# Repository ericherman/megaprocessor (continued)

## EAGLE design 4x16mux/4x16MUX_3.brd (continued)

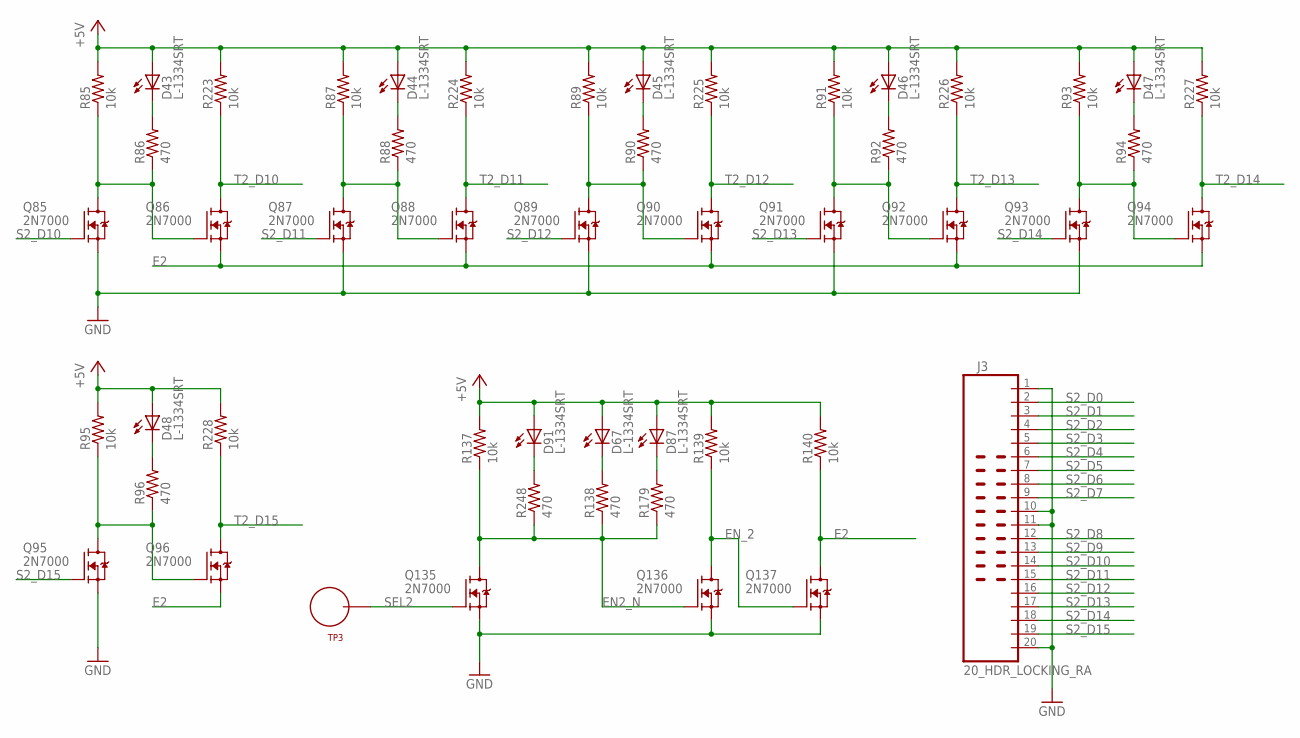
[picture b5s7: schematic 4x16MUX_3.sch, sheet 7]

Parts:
D43, D44, D45, D46, D47, D48, D67, D87, D91: L-1334SRT; LED3MM
J3: 20_HDR_LOCKING_RA
Q85, Q86, Q87, Q88, Q89, Q90, Q91, Q92, Q93, Q94, Q95, Q96, Q135, Q136, Q137: 2N7000; TO92-DGS
R85, R87, R89, R91, R93, R95, R137, R139, R140, R223, R224, R225, R226, R227, R228: 10k; R_P2INCH
R86, R88, R90, R92, R94, R96, R138, R179, R248: 470; R_P2INCH
TP3: TEST_LOOP

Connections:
+5V: D43.A, D44.A, D45.A, D46.A, D47.A, D48.A, D67.A, D87.A, D91.A, R85.2, R87.2, R89.2, R91.2, R93.2, R95.2, R137.2, R139.2, R140.2, R223.2, R224.2, R225.2, R226.2, R227.2, R228.2; also elsewhere on the board
E2: Q86.S, Q88.S, Q90.S, Q92.S, Q94.S, Q96.S, Q137.D, R140.1; also elsewhere on the board
EN2_N: Q135.D, Q136.G, R137.1, R138.1, R179.1, R248.1; also elsewhere on the board
EN_2: Q136.D, Q137.G, R139.1
GND: J3.1, J3.10, J3.11, J3.20, Q85.S, Q87.S, Q89.S, Q91.S, Q93.S, Q95.S, Q135.S, Q136.S, Q137.S; also elsewhere on the board
unnamed: Q85.D, Q86.G, R85.1, R86.1
unnamed: D43.K (C), R86.2
unnamed: Q87.D, Q88.G, R87.1, R88.1
unnamed: D44.K (C), R88.2
unnamed: Q89.D, Q90.G, R89.1, R90.1
unnamed: D45.K (C), R90.2
unnamed: Q91.D, Q92.G, R91.1, R92.1
unnamed: D46.K (C), R92.2
unnamed: Q93.D, Q94.G, R93.1, R94.1
unnamed: D47.K (C), R94.2
unnamed: Q95.D, Q96.G, R95.1, R96.1
unnamed: D48.K (C), R96.2
unnamed: D67.K (C), R138.2
unnamed: D87.K (C), R179.2
unnamed: D91.K (C), R248.2
S2_D0: J3.2; also elsewhere on the board
S2_D1: J3.3; also elsewhere on the board
S2_D2: J3.4; also elsewhere on the board
S2_D3: J3.5; also elsewhere on the board
S2_D4: J3.6; also elsewhere on the board
S2_D5: J3.7; also elsewhere on the board
S2_D6: J3.8; also elsewhere on the board
S2_D7: J3.9; also elsewhere on the board
S2_D8: J3.12; also elsewhere on the board
S2_D9: J3.13; also elsewhere on the board
S2_D10: J3.14, Q85.G
S2_D11: J3.15, Q87.G
S2_D12: J3.16, Q89.G
S2_D13: J3.17, Q91.G
S2_D14: J3.18, Q93.G
S2_D15: J3.19, Q95.G
SEL2: Q135.G, TP3.P$1
T2_D10: Q86.D, R223.1; also elsewhere on the board
T2_D11: Q88.D, R224.1; also elsewhere on the board
T2_D12: Q90.D, R225.1; also elsewhere on the board
T2_D13: Q92.D, R226.1; also elsewhere on the board
T2_D14: Q94.D, R227.1; also elsewhere on the board
T2_D15: Q96.D, R228.1; also elsewhere on the board

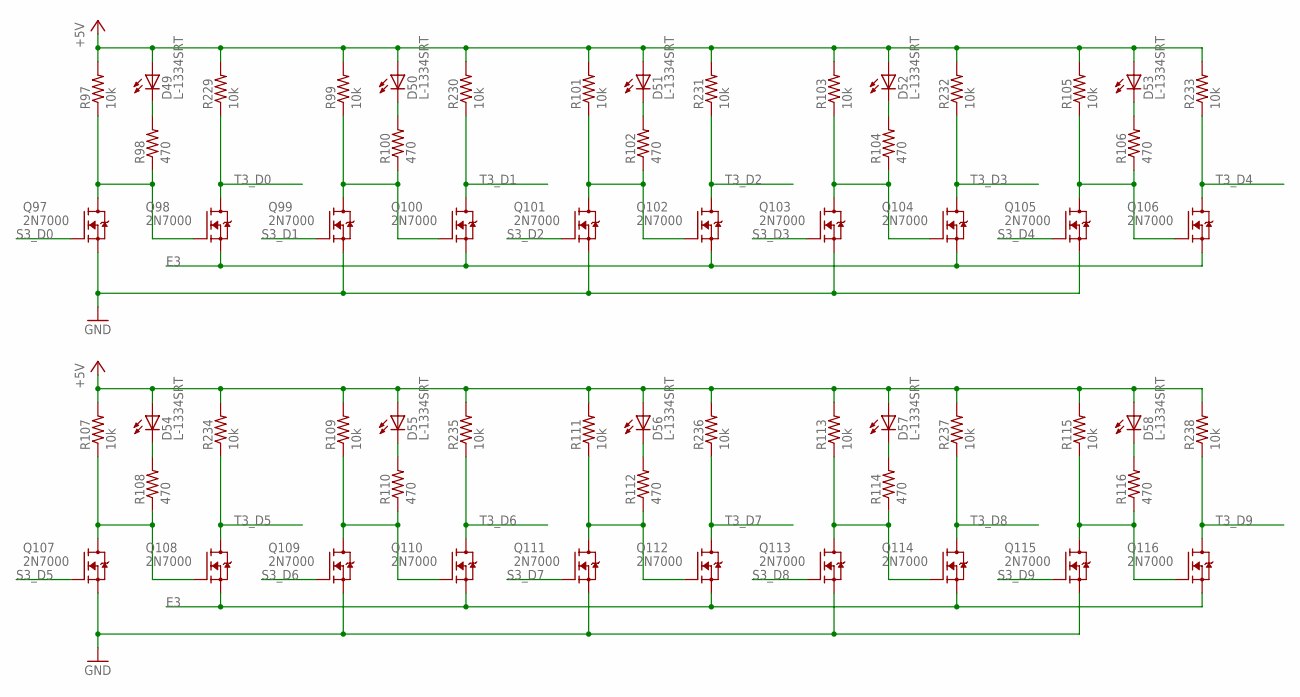
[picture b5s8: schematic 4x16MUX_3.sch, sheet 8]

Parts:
D49, D50, D51, D52, D53, D54, D55, D56, D57, D58: L-1334SRT; LED3MM
Q97, Q98, Q99, Q100, Q101, Q102, Q103, Q104, Q105, Q106, Q107, Q108, Q109, Q110, Q111, Q112, Q113, Q114, Q115, Q116: 2N7000; TO92-DGS
R97, R99, R101, R103, R105, R107, R109, R111, R113, R115, R229, R230, R231, R232, R233, R234, R235, R236, R237, R238: 10k; R_P2INCH
R98, R100, R102, R104, R106, R108, R110, R112, R114, R116: 470; R_P2INCH

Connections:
+5V: D49.A, D50.A, D51.A, D52.A, D53.A, D54.A, D55.A, D56.A, D57.A, D58.A, R97.2, R99.2, R101.2, R103.2, R105.2, R107.2, R109.2, R111.2, R113.2, R115.2, R229.2, R230.2, R231.2, R232.2, R233.2, R234.2, R235.2, R236.2, R237.2, R238.2; also elsewhere on the board
E3: Q98.S, Q100.S, Q102.S, Q104.S, Q106.S, Q108.S, Q110.S, Q112.S, Q114.S, Q116.S; also elsewhere on the board
GND: Q97.S, Q99.S, Q101.S, Q103.S, Q105.S, Q107.S, Q109.S, Q111.S, Q113.S, Q115.S; also elsewhere on the board
unnamed: Q97.D, Q98.G, R97.1, R98.1
unnamed: D49.K (C), R98.2
unnamed: Q99.D, Q100.G, R99.1, R100.1
unnamed: D50.K (C), R100.2
unnamed: Q101.D, Q102.G, R101.1, R102.1
unnamed: D51.K (C), R102.2
unnamed: Q103.D, Q104.G, R103.1, R104.1
unnamed: D52.K (C), R104.2
unnamed: Q105.D, Q106.G, R105.1, R106.1
unnamed: D53.K (C), R106.2
unnamed: Q107.D, Q108.G, R107.1, R108.1
unnamed: D54.K (C), R108.2
unnamed: Q109.D, Q110.G, R109.1, R110.1
unnamed: D55.K (C), R110.2
unnamed: Q111.D, Q112.G, R111.1, R112.1
unnamed: D56.K (C), R112.2
unnamed: Q113.D, Q114.G, R113.1, R114.1
unnamed: D57.K (C), R114.2
unnamed: Q115.D, Q116.G, R115.1, R116.1
unnamed: D58.K (C), R116.2
S3_D0: Q97.G; also elsewhere on the board
S3_D1: Q99.G; also elsewhere on the board
S3_D2: Q101.G; also elsewhere on the board
S3_D3: Q103.G; also elsewhere on the board
S3_D4: Q105.G; also elsewhere on the board
S3_D5: Q107.G; also elsewhere on the board
S3_D6: Q109.G; also elsewhere on the board
S3_D7: Q111.G; also elsewhere on the board
S3_D8: Q113.G; also elsewhere on the board
S3_D9: Q115.G; also elsewhere on the board
T3_D0: Q98.D, R229.1; also elsewhere on the board
T3_D1: Q100.D, R230.1; also elsewhere on the board
T3_D2: Q102.D, R231.1; also elsewhere on the board
T3_D3: Q104.D, R232.1; also elsewhere on the board
T3_D4: Q106.D, R233.1; also elsewhere on the board
T3_D5: Q108.D, R234.1; also elsewhere on the board
T3_D6: Q110.D, R235.1; also elsewhere on the board
T3_D7: Q112.D, R236.1; also elsewhere on the board
T3_D8: Q114.D, R237.1; also elsewhere on the board
T3_D9: Q116.D, R238.1; also elsewhere on the board

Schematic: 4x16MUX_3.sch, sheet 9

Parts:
D59, D60, D61, D62, D63, D64, D68, D88, D92: L-1334SRT; LED3MM
J4: 20_HDR_LOCKING_RA
Q117, Q118, Q119, Q120, Q121, Q122, Q123, Q124, Q125, Q126, Q127, Q128, Q138, Q139, Q140: 2N7000; TO92-DGS
R117, R119, R121, R123, R125, R127, R141, R143, R144, R239, R240, R241, R242, R243, R244: 10k; R_P2INCH
R118, R120, R122, R124, R126, R128, R142, R180, R249: 470; R_P2INCH
TP4: TEST_LOOP

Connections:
+5V: D59.A, D60.A, D61.A, D62.A, D63.A, D64.A, D68.A, D88.A, D92.A, R117.2, R119.2, R121.2, R123.2, R125.2, R127.2, R141.2, R143.2, R144.2, R239.2, R240.2, R241.2, R242.2, R243.2, R244.2; also elsewhere on the board
E3: Q118.S, Q120.S, Q122.S, Q124.S, Q126.S, Q128.S, Q140.D, R144.1; also elsewhere on the board
EN3_N: Q138.D, Q139.G, R141.1, R142.1, R180.1, R249.1; also elsewhere on the board
EN_3: Q139.D, Q140.G, R143.1
GND: J4.1, J4.10, J4.11, J4.20, Q117.S, Q119.S, Q121.S, Q123.S, Q125.S, Q127.S, Q138.S, Q139.S, Q140.S; also elsewhere on the board
unnamed: Q117.D, Q118.G, R117.1, R118.1
unnamed: D59.K (C), R118.2
unnamed: Q119.D, Q120.G, R119.1, R120.1
unnamed: D60.K (C), R120.2
unnamed: Q121.D, Q122.G, R121.1, R122.1
unnamed: D61.K (C), R122.2
unnamed: Q123.D, Q124.G, R123.1, R124.1
unnamed: D62.K (C), R124.2
unnamed: Q125.D, Q126.G, R125.1, R126.1
unnamed: D63.K (C), R126.2
unnamed: Q127.D, Q128.G, R127.1, R128.1
unnamed: D64.K (C), R128.2
unnamed: D68.K (C), R142.2
unnamed: D88.K (C), R180.2
unnamed: D92.K (C), R249.2
S3_D0: J4.2; also elsewhere on the board
S3_D1: J4.3; also elsewhere on the board
S3_D2: J4.4; also elsewhere on the board
S3_D3: J4.5; also elsewhere on the board
S3_D4: J4.6; also elsewhere on the board
S3_D5: J4.7; also elsewhere on the board
S3_D6: J4.8; also elsewhere on the board
S3_D7: J4.9; also elsewhere on the board
S3_D8: J4.12; also elsewhere on the board
S3_D9: J4.13; also elsewhere on the board
S3_D10: J4.14, Q117.G
S3_D11: J4.15, Q119.G
S3_D12: J4.16, Q121.G
S3_D13: J4.17, Q123.G
S3_D14: J4.18, Q125.G
S3_D15: J4.19, Q127.G
SEL3: Q138.G, TP4.P$1
T3_D10: Q118.D, R239.1; also elsewhere on the board
T3_D11: Q120.D, R240.1; also elsewhere on the board
T3_D12: Q122.D, R241.1; also elsewhere on the board
T3_D13: Q124.D, R242.1; also elsewhere on the board
T3_D14: Q126.D, R243.1; also elsewhere on the board
T3_D15: Q128.D, R244.1; also elsewhere on the board

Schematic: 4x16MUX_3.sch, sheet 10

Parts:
D69, D70, D71, D72: L-1334SRT; LED3MM
Q141, Q142, Q143, Q144, Q145, Q146, Q147, Q148, Q149, Q150, Q151, Q152, Q153, Q154, Q155, Q156, Q157, Q158, Q159, Q160, Q221, Q222, Q223, Q224: 2N7000; TO92-DGS
R145, R147, R149, R151, R250, R253, R254, R255: 10k; R_P2INCH
R146, R148, R150, R152: 470; R_P2INCH

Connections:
+5V: D69.A, D70.A, D71.A, D72.A, R145.2, R147.2, R149.2, R151.2, R250.2, R253.2, R254.2, R255.2; also elsewhere on the board
DOUT0: Q142.D, R250.1; also elsewhere on the board
DOUT1: Q147.D, R253.1; also elsewhere on the board
DOUT2: Q152.D, R254.1; also elsewhere on the board
DOUT3: Q157.D, R255.1; also elsewhere on the board
FORCE_ZERO_N: Q221.G, Q222.G, Q223.G, Q224.G; also elsewhere on the board
GND: Q142.S, Q145.S, Q147.S, Q150.S, Q152.S, Q155.S, Q157.S, Q160.S; also elsewhere on the board
unnamed: Q142.G, Q221.D, R145.1, R146.1
unnamed: D69.K (C), R146.2
unnamed: Q144.S, Q145.D
unnamed: Q143.S, Q144.D
unnamed: Q141.S, Q143.D
unnamed: Q147.G, Q222.D, R147.1, R148.1
unnamed: D70.K (C), R148.2
unnamed: Q149.S, Q150.D
unnamed: Q148.S, Q149.D
unnamed: Q146.S, Q148.D
unnamed: Q152.G, Q223.D, R149.1, R150.1
unnamed: D71.K (C), R150.2
unnamed: Q154.S, Q155.D
unnamed: Q153.S, Q154.D
unnamed: Q151.S, Q153.D
unnamed: Q157.G, Q224.D, R151.1, R152.1
unnamed: D72.K (C), R152.2
unnamed: Q159.S, Q160.D
unnamed: Q158.S, Q159.D
unnamed: Q156.S, Q158.D
unnamed: Q141.D, Q221.S
unnamed: Q146.D, Q222.S
unnamed: Q151.D, Q223.S
unnamed: Q156.D, Q224.S
T0_D0: Q141.G; also elsewhere on the board
T0_D1: Q146.G; also elsewhere on the board
T0_D2: Q151.G; also elsewhere on the board
T0_D3: Q156.G; also elsewhere on the board
T1_D0: Q143.G; also elsewhere on the board
T1_D1: Q148.G; also elsewhere on the board
T1_D2: Q153.G; also elsewhere on the board
T1_D3: Q158.G; also elsewhere on the board
T2_D0: Q144.G; also elsewhere on the board
T2_D1: Q149.G; also elsewhere on the board
T2_D2: Q154.G; also elsewhere on the board
T2_D3: Q159.G; also elsewhere on the board
T3_D0: Q145.G; also elsewhere on the board
T3_D1: Q150.G; also elsewhere on the board
T3_D2: Q155.G; also elsewhere on the board
T3_D3: Q160.G; also elsewhere on the board

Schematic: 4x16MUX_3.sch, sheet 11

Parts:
D73, D74, D75, D76: L-1334SRT; LED3MM
Q161, Q162, Q163, Q164, Q165, Q166, Q167, Q168, Q169, Q170, Q171, Q172, Q173, Q174, Q175, Q176, Q177, Q178, Q179, Q180, Q225, Q226, Q227, Q228: 2N7000; TO92-DGS
R153, R155, R157, R159, R256, R257, R258, R259: 10k; R_P2INCH
R154, R156, R158, R160: 470; R_P2INCH

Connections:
+5V: D73.A, D74.A, D75.A, D76.A, R153.2, R155.2, R157.2, R159.2, R256.2, R257.2, R258.2, R259.2; also elsewhere on the board
DOUT4: Q162.D, R256.1; also elsewhere on the board
DOUT5: Q167.D, R257.1; also elsewhere on the board
DOUT6: Q172.D, R258.1; also elsewhere on the board
DOUT7: Q177.D, R259.1; also elsewhere on the board
FORCE_ZERO_N: Q225.G, Q226.G, Q227.G, Q228.G; also elsewhere on the board
GND: Q162.S, Q165.S, Q167.S, Q170.S, Q172.S, Q175.S, Q177.S, Q180.S; also elsewhere on the board
unnamed: Q162.G, Q225.D, R153.1, R154.1
unnamed: D73.K (C), R154.2
unnamed: Q164.S, Q165.D
unnamed: Q163.S, Q164.D
unnamed: Q161.S, Q163.D
unnamed: Q167.G, Q226.D, R155.1, R156.1
unnamed: D74.K (C), R156.2
unnamed: Q169.S, Q170.D
unnamed: Q168.S, Q169.D
unnamed: Q166.S, Q168.D
unnamed: Q172.G, Q227.D, R157.1, R158.1
unnamed: D75.K (C), R158.2
unnamed: Q174.S, Q175.D
unnamed: Q173.S, Q174.D
unnamed: Q171.S, Q173.D
unnamed: Q177.G, Q228.D, R159.1, R160.1
unnamed: D76.K (C), R160.2
unnamed: Q179.S, Q180.D
unnamed: Q178.S, Q179.D
unnamed: Q176.S, Q178.D
unnamed: Q161.D, Q225.S
unnamed: Q166.D, Q226.S
unnamed: Q171.D, Q227.S
unnamed: Q176.D, Q228.S
T0_D4: Q161.G; also elsewhere on the board
T0_D5: Q166.G; also elsewhere on the board
T0_D6: Q171.G; also elsewhere on the board
T0_D7: Q176.G; also elsewhere on the board
T1_D4: Q163.G; also elsewhere on the board
T1_D5: Q168.G; also elsewhere on the board
T1_D6: Q173.G; also elsewhere on the board
T1_D7: Q178.G; also elsewhere on the board
T2_D4: Q164.G; also elsewhere on the board
T2_D5: Q169.G; also elsewhere on the board
T2_D6: Q174.G; also elsewhere on the board
T2_D7: Q179.G; also elsewhere on the board
T3_D4: Q165.G; also elsewhere on the board
T3_D5: Q170.G; also elsewhere on the board
T3_D6: Q175.G; also elsewhere on the board
T3_D7: Q180.G; also elsewhere on the board

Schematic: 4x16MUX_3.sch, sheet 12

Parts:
D77, D78, D79, D80: L-1334SRT; LED3MM
Q181, Q182, Q183, Q184, Q185, Q186, Q187, Q188, Q189, Q190, Q191, Q192, Q193, Q194, Q195, Q196, Q197, Q198, Q199, Q200, Q229, Q230, Q231, Q232: 2N7000; TO92-DGS
R161, R163, R165, R167, R260, R261, R262, R263: 10k; R_P2INCH
R162, R164, R166, R168: 470; R_P2INCH

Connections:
+5V: D77.A, D78.A, D79.A, D80.A, R161.2, R163.2, R165.2, R167.2, R260.2, R261.2, R262.2, R263.2; also elsewhere on the board
DOUT8: Q182.D, R260.1; also elsewhere on the board
DOUT9: Q187.D, R261.1; also elsewhere on the board
DOUT10: Q192.D, R262.1; also elsewhere on the board
DOUT11: Q197.D, R263.1; also elsewhere on the board
FORCE_ZERO_N: Q229.G, Q230.G, Q231.G, Q232.G; also elsewhere on the board
GND: Q182.S, Q185.S, Q187.S, Q190.S, Q192.S, Q195.S, Q197.S, Q200.S; also elsewhere on the board
unnamed: Q182.G, Q229.D, R161.1, R162.1
unnamed: D77.K (C), R162.2
unnamed: Q184.S, Q185.D
unnamed: Q183.S, Q184.D
unnamed: Q181.S, Q183.D
unnamed: Q187.G, Q230.D, R163.1, R164.1
unnamed: D78.K (C), R164.2
unnamed: Q189.S, Q190.D
unnamed: Q188.S, Q189.D
unnamed: Q186.S, Q188.D
unnamed: Q192.G, Q231.D, R165.1, R166.1
unnamed: D79.K (C), R166.2
unnamed: Q194.S, Q195.D
unnamed: Q193.S, Q194.D
unnamed: Q191.S, Q193.D
unnamed: Q197.G, Q232.D, R167.1, R168.1
unnamed: D80.K (C), R168.2
unnamed: Q199.S, Q200.D
unnamed: Q198.S, Q199.D
unnamed: Q196.S, Q198.D
unnamed: Q181.D, Q229.S
unnamed: Q186.D, Q230.S
unnamed: Q191.D, Q231.S
unnamed: Q196.D, Q232.S
T0_D8: Q181.G; also elsewhere on the board
T0_D9: Q186.G; also elsewhere on the board
T0_D10: Q191.G; also elsewhere on the board
T0_D11: Q196.G; also elsewhere on the board
T1_D8: Q183.G; also elsewhere on the board
T1_D9: Q188.G; also elsewhere on the board
T1_D10: Q193.G; also elsewhere on the board
T1_D11: Q198.G; also elsewhere on the board
T2_D8: Q184.G; also elsewhere on the board
T2_D9: Q189.G; also elsewhere on the board
T2_D10: Q194.G; also elsewhere on the board
T2_D11: Q199.G; also elsewhere on the board
T3_D8: Q185.G; also elsewhere on the board
T3_D9: Q190.G; also elsewhere on the board
T3_D10: Q195.G; also elsewhere on the board
T3_D11: Q200.G; also elsewhere on the board

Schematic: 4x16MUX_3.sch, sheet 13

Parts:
D81, D82, D83, D84: L-1334SRT; LED3MM
Q201, Q202, Q203, Q204, Q205, Q206, Q207, Q208, Q209, Q210, Q211, Q212, Q213, Q214, Q215, Q216, Q217, Q218, Q219, Q220, Q233, Q234, Q235, Q236: 2N7000; TO92-DGS
R169, R171, R173, R175, R264, R265, R266, R267: 10k; R_P2INCH
R170, R172, R174, R176: 470; R_P2INCH

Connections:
+5V: D81.A, D82.A, D83.A, D84.A, R169.2, R171.2, R173.2, R175.2, R264.2, R265.2, R266.2, R267.2; also elsewhere on the board
DOUT12: Q202.D, R264.1; also elsewhere on the board
DOUT13: Q207.D, R265.1; also elsewhere on the board
DOUT14: Q212.D, R266.1; also elsewhere on the board
DOUT15: Q217.D, R267.1; also elsewhere on the board
FORCE_ZERO_N: Q233.G, Q234.G, Q235.G, Q236.G; also elsewhere on the board
GND: Q202.S, Q205.S, Q207.S, Q210.S, Q212.S, Q215.S, Q217.S, Q220.S; also elsewhere on the board
unnamed: Q202.G, Q233.D, R169.1, R170.1
unnamed: D81.K (C), R170.2
unnamed: Q204.S, Q205.D
unnamed: Q203.S, Q204.D
unnamed: Q201.S, Q203.D
unnamed: Q207.G, Q234.D, R171.1, R172.1
unnamed: D82.K (C), R172.2
unnamed: Q209.S, Q210.D
unnamed: Q208.S, Q209.D
unnamed: Q206.S, Q208.D
unnamed: Q212.G, Q235.D, R173.1, R174.1
unnamed: D83.K (C), R174.2
unnamed: Q214.S, Q215.D
unnamed: Q213.S, Q214.D
unnamed: Q211.S, Q213.D
unnamed: Q217.G, Q236.D, R175.1, R176.1
unnamed: D84.K (C), R176.2
unnamed: Q219.S, Q220.D
unnamed: Q218.S, Q219.D
unnamed: Q216.S, Q218.D
unnamed: Q201.D, Q233.S
unnamed: Q206.D, Q234.S
unnamed: Q211.D, Q235.S
unnamed: Q216.D, Q236.S
T0_D12: Q201.G; also elsewhere on the board
T0_D13: Q206.G; also elsewhere on the board
T0_D14: Q211.G; also elsewhere on the board
T0_D15: Q216.G; also elsewhere on the board
T1_D12: Q203.G; also elsewhere on the board
T1_D13: Q208.G; also elsewhere on the board
T1_D14: Q213.G; also elsewhere on the board
T1_D15: Q218.G; also elsewhere on the board
T2_D12: Q204.G; also elsewhere on the board
T2_D13: Q209.G; also elsewhere on the board
T2_D14: Q214.G; also elsewhere on the board
T2_D15: Q219.G; also elsewhere on the board
T3_D12: Q205.G; also elsewhere on the board
T3_D13: Q210.G; also elsewhere on the board
T3_D14: Q215.G; also elsewhere on the board
T3_D15: Q220.G; also elsewhere on the board

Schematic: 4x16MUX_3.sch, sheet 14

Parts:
D93: L-1334SRT; LED3MM
J5: 20_HDR_LOCKING_RA
Q237, Q238, Q239, Q240, Q241, Q242: 2N7000; TO92-DGS
R245, R252, R268: 10k; R_P2INCH
R251: 470; R_P2INCH

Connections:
+5V: R245.2, R251.2, R252.2, R268.2; also elsewhere on the board
DOUT0: J5.2; also elsewhere on the board
DOUT1: J5.3; also elsewhere on the board
DOUT2: J5.4; also elsewhere on the board
DOUT3: J5.5; also elsewhere on the board
DOUT4: J5.6; also elsewhere on the board
DOUT5: J5.7; also elsewhere on the board
DOUT6: J5.8; also elsewhere on the board
DOUT7: J5.9; also elsewhere on the board
DOUT8: J5.12; also elsewhere on the board
DOUT9: J5.13; also elsewhere on the board
DOUT10: J5.14; also elsewhere on the board
DOUT11: J5.15; also elsewhere on the board
DOUT12: J5.16; also elsewhere on the board
DOUT13: J5.17; also elsewhere on the board
DOUT14: J5.18; also elsewhere on the board
DOUT15: J5.19; also elsewhere on the board
EN0_N: Q238.G; also elsewhere on the board
EN1_N: Q239.G; also elsewhere on the board
EN2_N: Q240.G; also elsewhere on the board
EN3_N: Q237.G; also elsewhere on the board
FORCE_ZERO: Q241.D, Q242.G, R252.1
FORCE_ZERO_N: Q242.D, R268.1; also elsewhere on the board
GND: J5.1, J5.10, J5.11, J5.20, Q237.S, Q241.S, Q242.S; also elsewhere on the board
unnamed: D93.K (C), Q238.D, Q241.G, R245.1
unnamed: Q238.S, Q239.D
unnamed: Q239.S, Q240.D
unnamed: Q237.D, Q240.S
unnamed: D93.A, R251.1

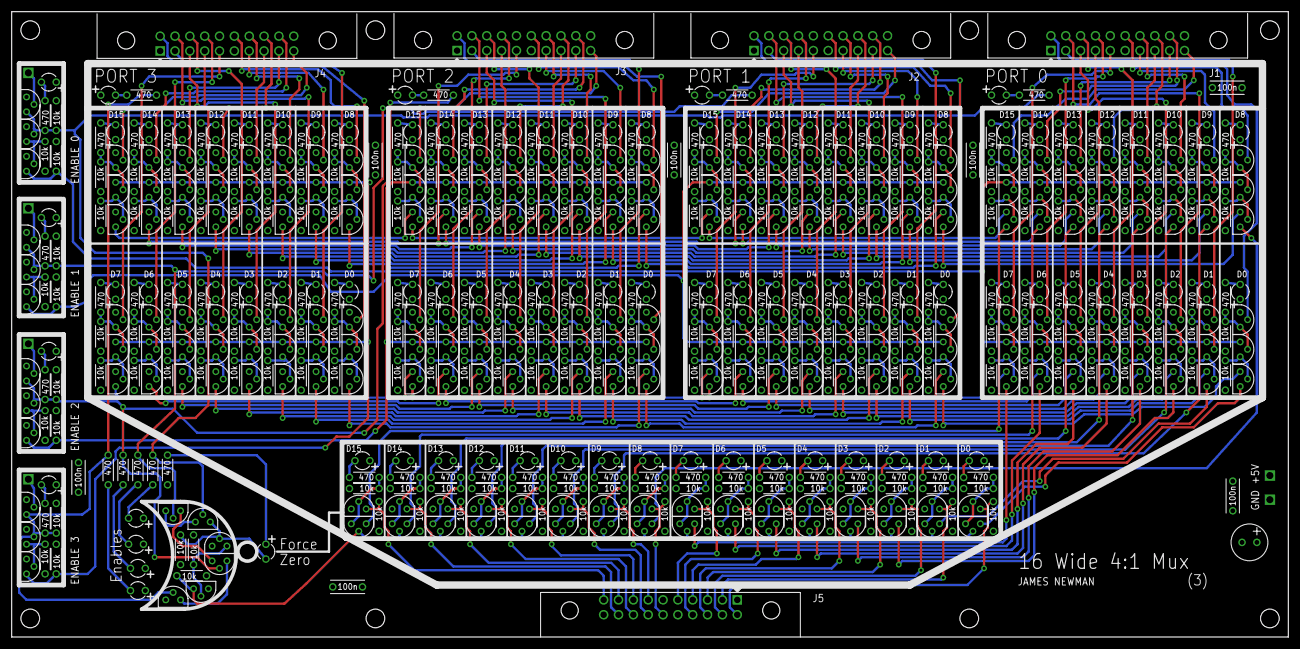
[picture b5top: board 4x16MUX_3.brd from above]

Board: 4 copper layers, 218.4 x 107.0 mm, 630 parts (0 on the bottom side), 405 nets.

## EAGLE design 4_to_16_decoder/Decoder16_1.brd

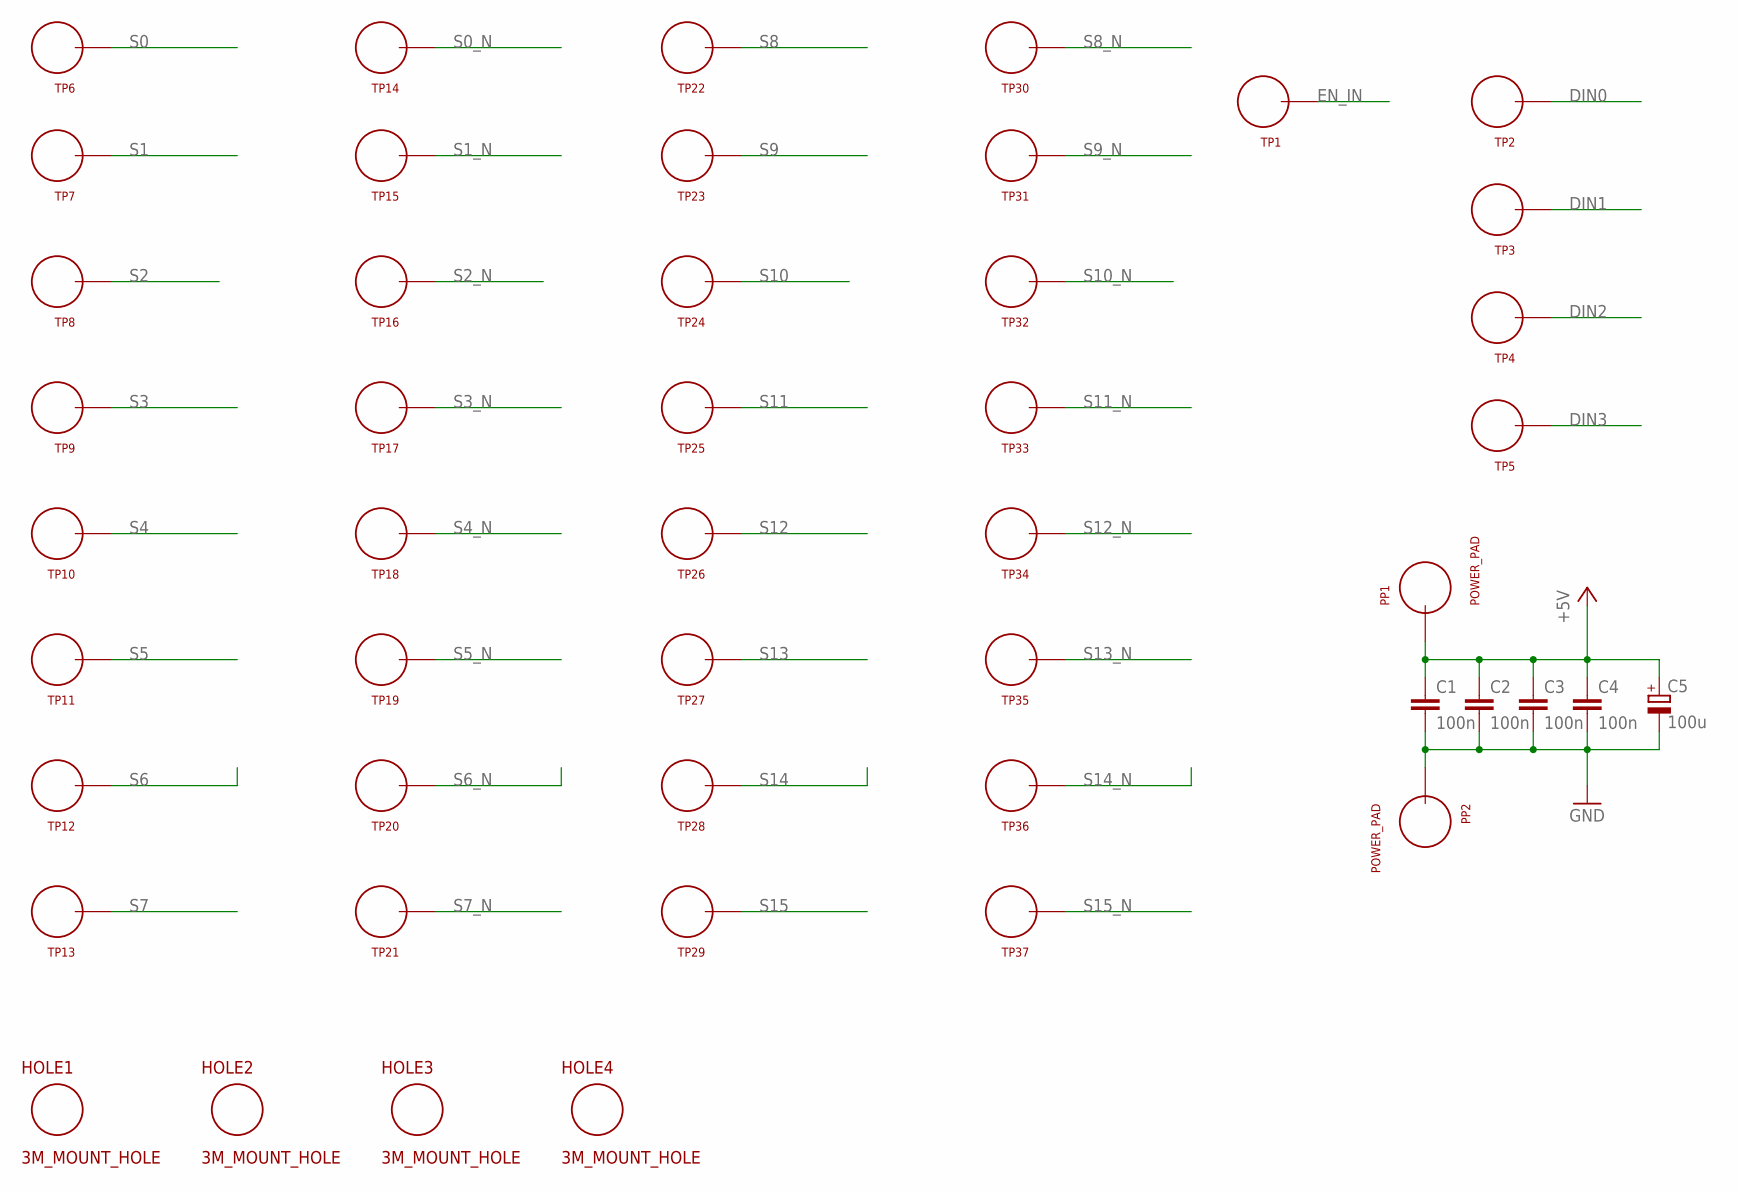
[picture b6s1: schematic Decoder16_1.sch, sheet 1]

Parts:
C1, C2, C3, C4: 100n; CAP_P2INCH
C5: 100u; POLARISED_CAP_2P5_6P3MM
HOLE1, HOLE2, HOLE3, HOLE4: 3M_MOUNT_HOLE; 3M_HOLE
PP1, PP2: POWER_PAD
TP1, TP2, TP3, TP4, TP5, TP6, TP7, TP8, TP9, TP10, TP11, TP12, TP13, TP14, TP15, TP16, TP17, TP18, TP19, TP20, TP21, TP22, TP23, TP24, TP25, TP26, TP27, TP28, TP29, TP30, TP31, TP32, TP33, TP34, TP35, TP36, TP37: TEST_LOOP

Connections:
+5V: C1.1, C2.1, C3.1, C4.1, C5.A, PP1.1; also elsewhere on the board
DIN0: TP2.P$1; also elsewhere on the board
DIN1: TP3.P$1; also elsewhere on the board
DIN2: TP4.P$1; also elsewhere on the board
DIN3: TP5.P$1; also elsewhere on the board
EN_IN: TP1.P$1; also elsewhere on the board
GND: C1.2, C2.2, C3.2, C4.2, C5.K, PP2.1; also elsewhere on the board
S0: TP6.P$1; also elsewhere on the board
S0_N: TP14.P$1; also elsewhere on the board
S1: TP7.P$1; also elsewhere on the board
S1_N: TP15.P$1; also elsewhere on the board
S2: TP8.P$1; also elsewhere on the board
S2_N: TP16.P$1; also elsewhere on the board
S3: TP9.P$1; also elsewhere on the board
S3_N: TP17.P$1; also elsewhere on the board
S4: TP10.P$1; also elsewhere on the board
S4_N: TP18.P$1; also elsewhere on the board
S5: TP11.P$1; also elsewhere on the board
S5_N: TP19.P$1; also elsewhere on the board
S6: TP12.P$1; also elsewhere on the board
S6_N: TP20.P$1; also elsewhere on the board
S7: TP13.P$1; also elsewhere on the board
S7_N: TP21.P$1; also elsewhere on the board
S8: TP22.P$1; also elsewhere on the board
S8_N: TP30.P$1; also elsewhere on the board
S9: TP23.P$1; also elsewhere on the board
S9_N: TP31.P$1; also elsewhere on the board
S10: TP24.P$1; also elsewhere on the board
S10_N: TP32.P$1; also elsewhere on the board
S11: TP25.P$1; also elsewhere on the board
S11_N: TP33.P$1; also elsewhere on the board
S12: TP26.P$1; also elsewhere on the board
S12_N: TP34.P$1; also elsewhere on the board
S13: TP27.P$1; also elsewhere on the board
S13_N: TP35.P$1; also elsewhere on the board
S14: TP28.P$1; also elsewhere on the board
S14_N: TP36.P$1; also elsewhere on the board
S15: TP29.P$1; also elsewhere on the board
S15_N: TP37.P$1; also elsewhere on the board

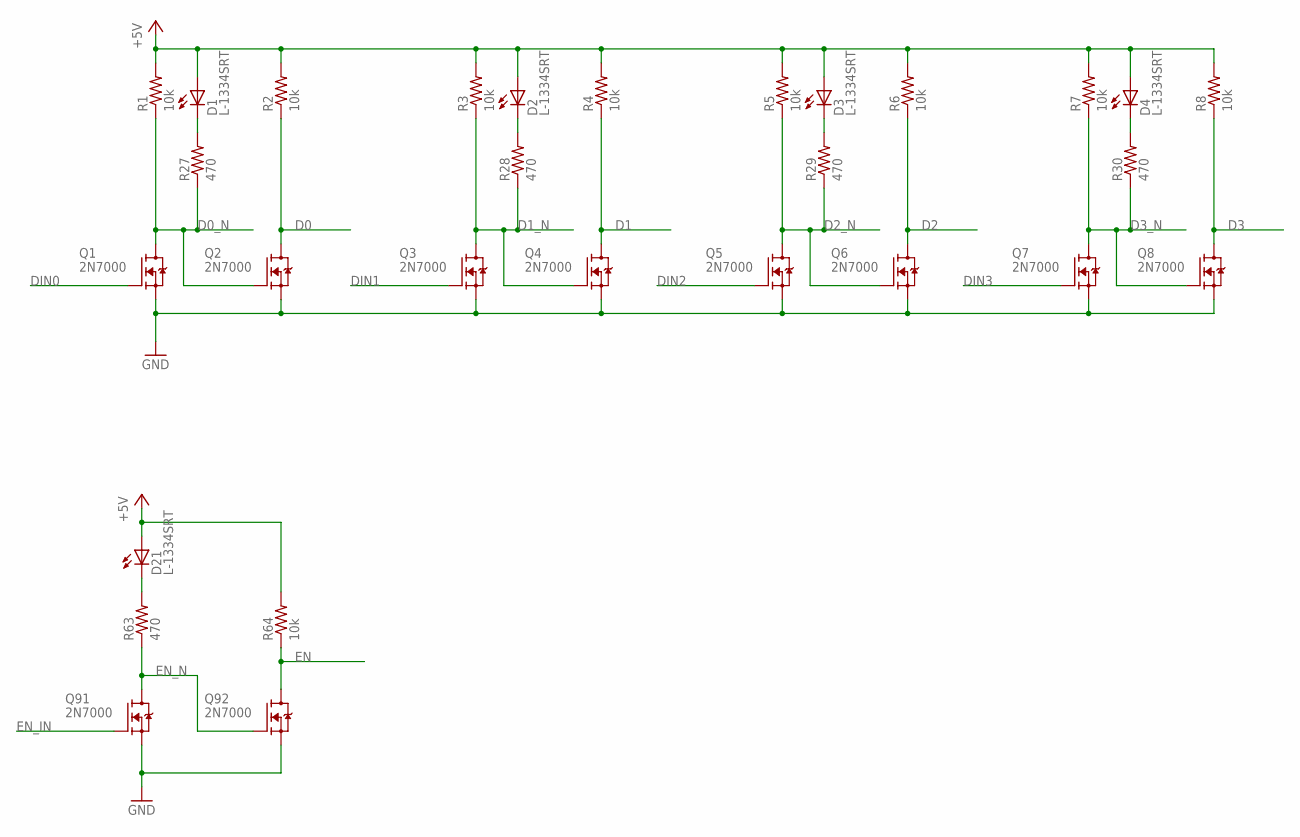
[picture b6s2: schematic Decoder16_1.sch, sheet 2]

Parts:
D1, D2, D3, D4, D21: L-1334SRT; LED3MM
Q1, Q2, Q3, Q4, Q5, Q6, Q7, Q8, Q91, Q92: 2N7000; TO92-DGS
R1, R2, R3, R4, R5, R6, R7, R8, R64: 10k; R_P2INCH
R27, R28, R29, R30, R63: 470; R_P2INCH

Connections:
+5V: D1.A, D2.A, D3.A, D4.A, D21.A, R1.2, R2.2, R3.2, R4.2, R5.2, R6.2, R7.2, R8.2, R64.2; also elsewhere on the board
D0: Q2.D, R2.1; also elsewhere on the board
D0_N: Q1.D, Q2.G, R1.1, R27.1; also elsewhere on the board
D1: Q4.D, R4.1; also elsewhere on the board
D1_N: Q3.D, Q4.G, R3.1, R28.1; also elsewhere on the board
D2: Q6.D, R6.1; also elsewhere on the board
D2_N: Q5.D, Q6.G, R5.1, R29.1; also elsewhere on the board
D3: Q8.D, R8.1; also elsewhere on the board
D3_N: Q7.D, Q8.G, R7.1, R30.1; also elsewhere on the board
DIN0: Q1.G; also elsewhere on the board
DIN1: Q3.G; also elsewhere on the board
DIN2: Q5.G; also elsewhere on the board
DIN3: Q7.G; also elsewhere on the board
EN: Q92.D, R64.1; also elsewhere on the board
EN_IN: Q91.G; also elsewhere on the board
EN_N: Q91.D, Q92.G, R63.1
GND: Q1.S, Q2.S, Q3.S, Q4.S, Q5.S, Q6.S, Q7.S, Q8.S, Q91.S, Q92.S; also elsewhere on the board
unnamed: D1.K (C), R27.2
unnamed: D2.K (C), R28.2
unnamed: D3.K (C), R29.2
unnamed: D4.K (C), R30.2
unnamed: D21.K (C), R63.2

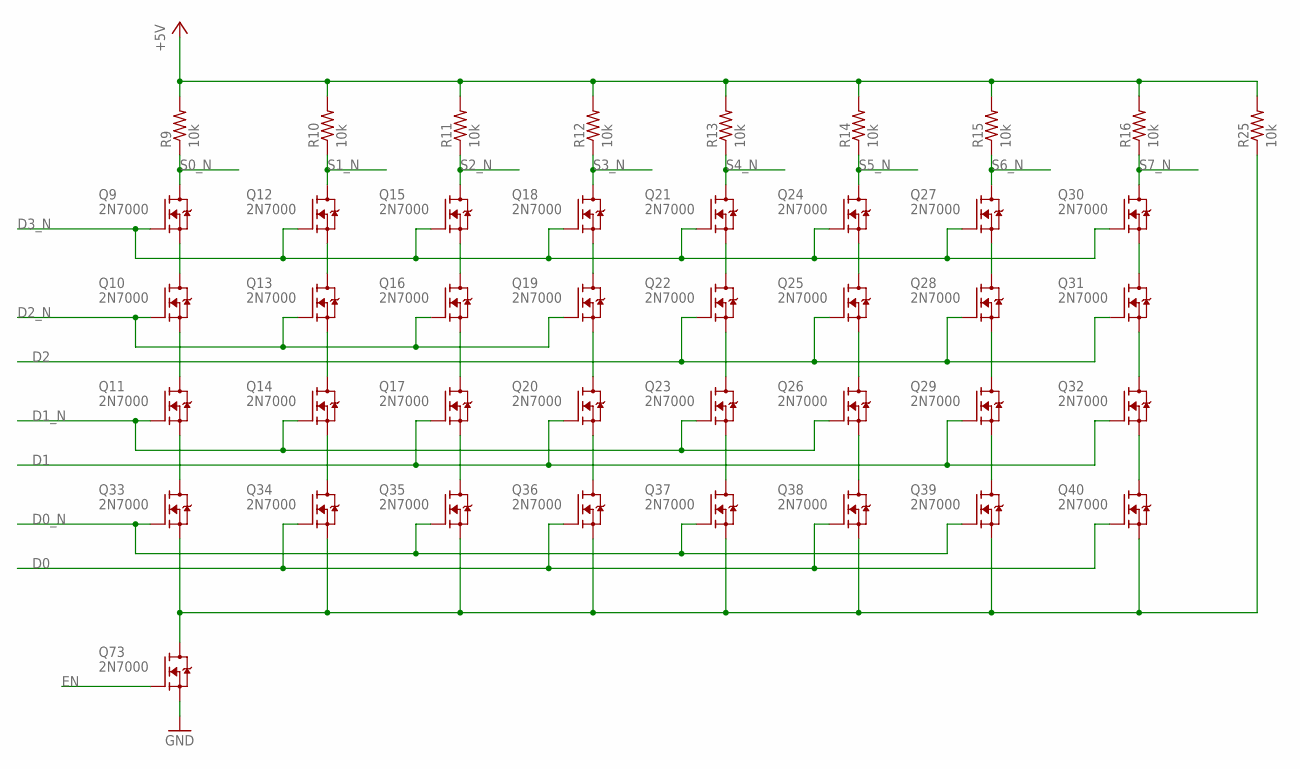
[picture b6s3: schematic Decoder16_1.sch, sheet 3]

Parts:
Q9, Q10, Q11, Q12, Q13, Q14, Q15, Q16, Q17, Q18, Q19, Q20, Q21, Q22, Q23, Q24, Q25, Q26, Q27, Q28, Q29, Q30, Q31, Q32, Q33, Q34, Q35, Q36, Q37, Q38, Q39, Q40, Q73: 2N7000; TO92-DGS
R9, R10, R11, R12, R13, R14, R15, R16, R25: 10k; R_P2INCH

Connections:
+5V: R9.2, R10.2, R11.2, R12.2, R13.2, R14.2, R15.2, R16.2, R25.2; also elsewhere on the board
D0: Q34.G, Q36.G, Q38.G, Q40.G; also elsewhere on the board
D0_N: Q33.G, Q35.G, Q37.G, Q39.G; also elsewhere on the board
D1: Q17.G, Q20.G, Q29.G, Q32.G; also elsewhere on the board
D1_N: Q11.G, Q14.G, Q23.G, Q26.G; also elsewhere on the board
D2: Q22.G, Q25.G, Q28.G, Q31.G; also elsewhere on the board
D2_N: Q10.G, Q13.G, Q16.G, Q19.G; also elsewhere on the board
D3_N: Q9.G, Q12.G, Q15.G, Q18.G, Q21.G, Q24.G, Q27.G, Q30.G; also elsewhere on the board
EN: Q73.G; also elsewhere on the board
GND: Q73.S; also elsewhere on the board
unnamed: Q9.S, Q10.D
unnamed: Q10.S, Q11.D
unnamed: Q12.S, Q13.D
unnamed: Q13.S, Q14.D
unnamed: Q15.S, Q16.D
unnamed: Q16.S, Q17.D
unnamed: Q18.S, Q19.D
unnamed: Q19.S, Q20.D
unnamed: Q21.S, Q22.D
unnamed: Q22.S, Q23.D
unnamed: Q24.S, Q25.D
unnamed: Q25.S, Q26.D
unnamed: Q27.S, Q28.D
unnamed: Q28.S, Q29.D
unnamed: Q30.S, Q31.D
unnamed: Q31.S, Q32.D
unnamed: Q11.S, Q33.D
unnamed: Q14.S, Q34.D
unnamed: Q17.S, Q35.D
unnamed: Q20.S, Q36.D
unnamed: Q23.S, Q37.D
unnamed: Q26.S, Q38.D
unnamed: Q29.S, Q39.D
unnamed: Q32.S, Q40.D
unnamed: Q33.S, Q34.S, Q35.S, Q36.S, Q37.S, Q38.S, Q39.S, Q40.S, Q73.D, R25.1
S0_N: Q9.D, R9.1; also elsewhere on the board
S1_N: Q12.D, R10.1; also elsewhere on the board
S2_N: Q15.D, R11.1; also elsewhere on the board
S3_N: Q18.D, R12.1; also elsewhere on the board
S4_N: Q21.D, R13.1; also elsewhere on the board
S5_N: Q24.D, R14.1; also elsewhere on the board
S6_N: Q27.D, R15.1; also elsewhere on the board
S7_N: Q30.D, R16.1; also elsewhere on the board

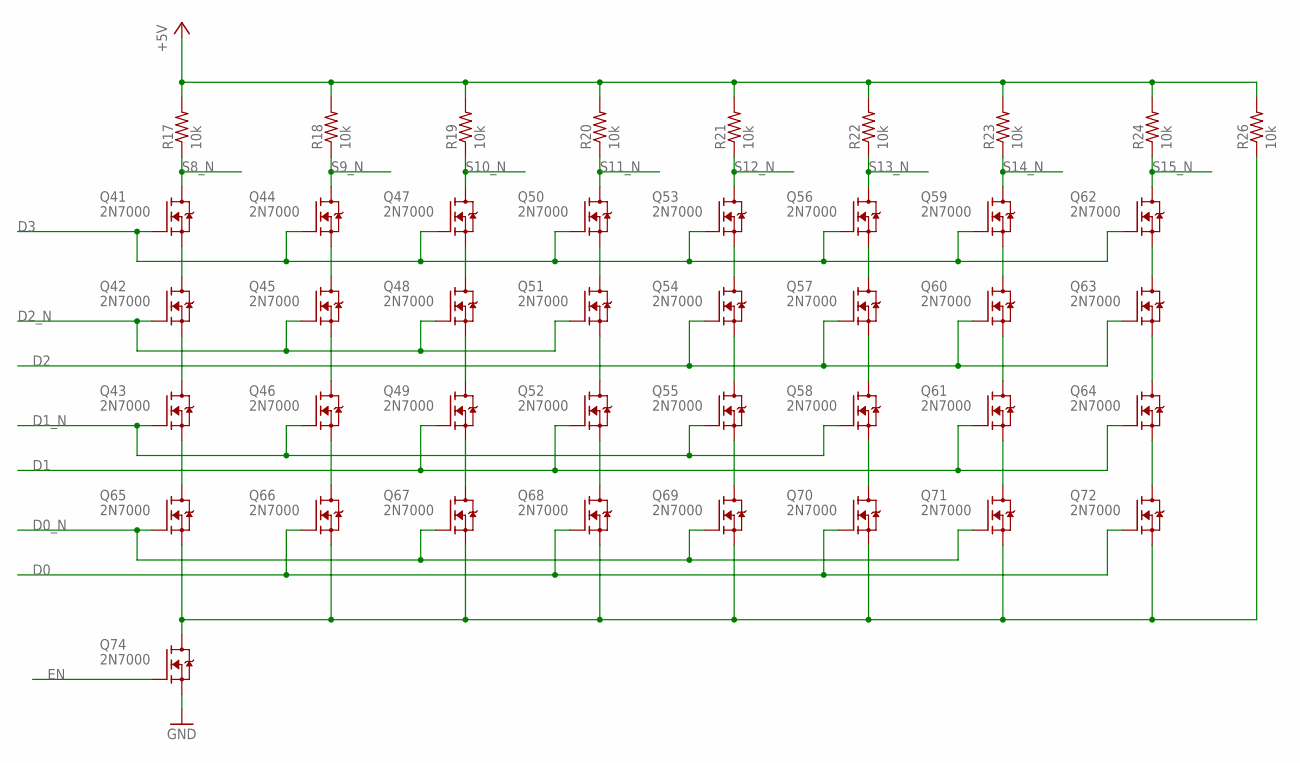
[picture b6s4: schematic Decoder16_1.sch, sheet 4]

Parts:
Q41, Q42, Q43, Q44, Q45, Q46, Q47, Q48, Q49, Q50, Q51, Q52, Q53, Q54, Q55, Q56, Q57, Q58, Q59, Q60, Q61, Q62, Q63, Q64, Q65, Q66, Q67, Q68, Q69, Q70, Q71, Q72, Q74: 2N7000; TO92-DGS
R17, R18, R19, R20, R21, R22, R23, R24, R26: 10k; R_P2INCH

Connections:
+5V: R17.2, R18.2, R19.2, R20.2, R21.2, R22.2, R23.2, R24.2, R26.2; also elsewhere on the board
D0: Q66.G, Q68.G, Q70.G, Q72.G; also elsewhere on the board
D0_N: Q65.G, Q67.G, Q69.G, Q71.G; also elsewhere on the board
D1: Q49.G, Q52.G, Q61.G, Q64.G; also elsewhere on the board
D1_N: Q43.G, Q46.G, Q55.G, Q58.G; also elsewhere on the board
D2: Q54.G, Q57.G, Q60.G, Q63.G; also elsewhere on the board
D2_N: Q42.G, Q45.G, Q48.G, Q51.G; also elsewhere on the board
D3: Q41.G, Q44.G, Q47.G, Q50.G, Q53.G, Q56.G, Q59.G, Q62.G; also elsewhere on the board
EN: Q74.G; also elsewhere on the board
GND: Q74.S; also elsewhere on the board
unnamed: Q41.S, Q42.D
unnamed: Q42.S, Q43.D
unnamed: Q44.S, Q45.D
unnamed: Q45.S, Q46.D
unnamed: Q47.S, Q48.D
unnamed: Q48.S, Q49.D
unnamed: Q50.S, Q51.D
unnamed: Q51.S, Q52.D
unnamed: Q53.S, Q54.D
unnamed: Q54.S, Q55.D
unnamed: Q56.S, Q57.D
unnamed: Q57.S, Q58.D
unnamed: Q59.S, Q60.D
unnamed: Q60.S, Q61.D
unnamed: Q62.S, Q63.D
unnamed: Q63.S, Q64.D
unnamed: Q43.S, Q65.D
unnamed: Q46.S, Q66.D
unnamed: Q49.S, Q67.D
unnamed: Q52.S, Q68.D
unnamed: Q55.S, Q69.D
unnamed: Q58.S, Q70.D
unnamed: Q61.S, Q71.D
unnamed: Q64.S, Q72.D
unnamed: Q65.S, Q66.S, Q67.S, Q68.S, Q69.S, Q70.S, Q71.S, Q72.S, Q74.D, R26.1
S8_N: Q41.D, R17.1; also elsewhere on the board
S9_N: Q44.D, R18.1; also elsewhere on the board
S10_N: Q47.D, R19.1; also elsewhere on the board
S11_N: Q50.D, R20.1; also elsewhere on the board
S12_N: Q53.D, R21.1; also elsewhere on the board
S13_N: Q56.D, R22.1; also elsewhere on the board
S14_N: Q59.D, R23.1; also elsewhere on the board
S15_N: Q62.D, R24.1; also elsewhere on the board
